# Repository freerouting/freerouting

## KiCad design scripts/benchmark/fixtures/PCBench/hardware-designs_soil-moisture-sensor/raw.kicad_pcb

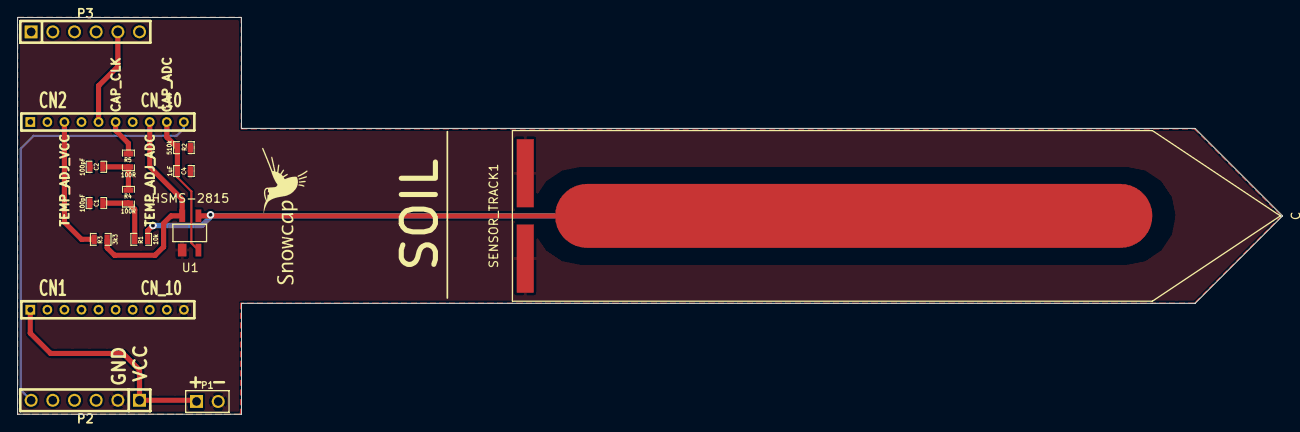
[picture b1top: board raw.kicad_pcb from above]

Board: 2 copper layers, 148.2 x 46.5 mm, 15 parts (0 on the bottom side), 11 nets.

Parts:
C1, C2: 100pF; SM0603_Capa
C4: 1uF; SM0603_Capa
CN1, CN2: CN_10; CONN-10-2MM
P1: CONN_2; PIN_ARRAY_2X1
P2, P3: CN_6; PIN_ARRAY-6X1
R1: 10k; SM0603_Resistor
R2: 510k; SM0603_Resistor
R3: 3k3; SM0603_Resistor
R4, R5: 100R; SM0603_Resistor
SENSOR_TRACK1: C; SOIL_SENSOR_CAPACITIVE
U1: HSMS-2815

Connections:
+3.3V: CN1.1, P1.1, P2.1
/CAP_ADC: C4.1, CN2.9, R2.1, U1.2
/CAP_CLK: CN2.6, R5.2
/TEMP_ADJ_ADC: CN2.8, R3.1, U1.3
/TEMP_ADJ_VCC: CN2.3, R3.2
/V_MEASURE1: CN2.10, P2.6
/V_MEASURE2: CN2.5, P3.5
GND: C1.1, C2.1, C4.2, CN1.10, P1.2, P2.2, R2.2, SENSOR_TRACK1.2, U1.1
unnamed: C2.2, R4.2, R5.1
unnamed: C1.2, R1.2, R4.1
unnamed: R1.1, SENSOR_TRACK1.1, U1.4

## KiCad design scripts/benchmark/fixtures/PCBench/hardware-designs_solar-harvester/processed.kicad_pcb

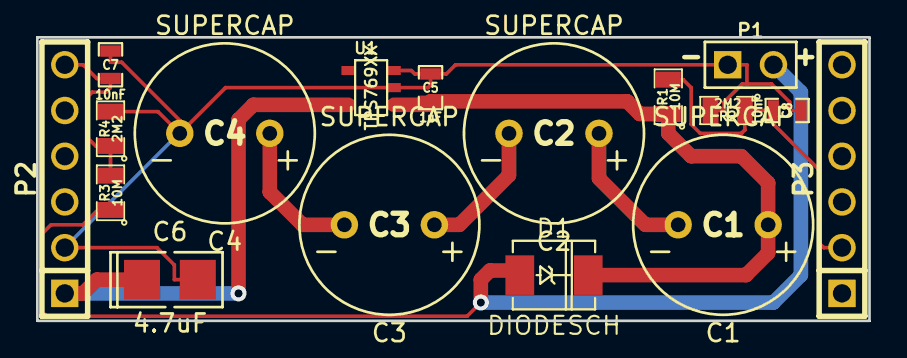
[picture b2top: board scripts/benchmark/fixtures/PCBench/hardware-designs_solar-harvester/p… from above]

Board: 2 copper layers, 46.2 x 15.7 mm, 18 parts (1 on the bottom side), 9 nets.

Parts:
C1, C2, C3, C4: SUPERCAP; SUPERCAP_ESHSR-0010C0-002R7
C5: 1uF; SM0603_Capa
C6: 4.7uF; SM1411_POL
C7, C8: 10nF; SM0603_Capa
D1: DIODESCH; DO-214AC(SMA)
Noname_1: LOGO_SNOWCAP_BACK
P1: CONN_2; PIN_ARRAY_2X1
P2, P3: CONN_6; PIN_ARRAY-6X1
R1, R3: 10M; SM0805
R2, R4: 2M2; SM0805
U1: TPS769XX; SOT23-5

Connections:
/V_MEASURE1: C7.1, P2.6, R3.2, R4.1
/V_MEASURE2: C8.1, P3.2, R1.2, R2.1
GND: C4.2, C5.2, C6.2, C7.2, C8.2, P1.1, P2.2, R2.2, R4.2, U1.2, U1.3
unnamed: C2.2, C3.1
unnamed: D1.1, P1.2, R3.1
unnamed: C6.1, P2.1, U1.5
unnamed: C1.2, C2.1
unnamed: C1.1, C5.1, D1.2, R1.1, U1.1
unnamed: C3.2, C4.1

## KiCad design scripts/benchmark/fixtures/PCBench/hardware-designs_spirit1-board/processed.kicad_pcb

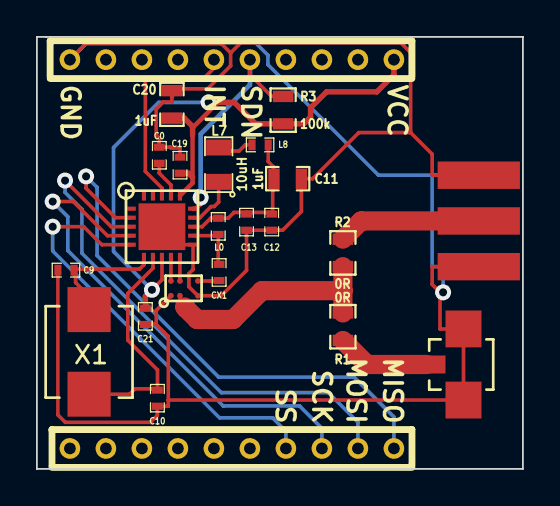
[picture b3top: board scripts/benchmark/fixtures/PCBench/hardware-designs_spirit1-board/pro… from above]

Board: 2 copper layers, 27.0 x 24.0 mm, 23 parts (1 on the bottom side), 21 nets.

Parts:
C0, C12: 100nF; SM0402_c
C9: 12pF; SM0402_c
C10: 10pF; SM0402_c
C11, C20: 1uF; SM0603_Capa
C13: 330pF; SM0402_c
C19: 10nF; SM0402_c
C21: 100pF; SM0402_c
CN1: RB-CN10; RB_CN10_2mm
CN2: ANT; RF_SMA
CN3: ANT; U.FL-R-SMT_01
CX1: C; SM0402_c
L0: 150nH; SM0402
L7: 10uH; SM0805
L8: 62nH; SM0402
Noname_1: LOGO_SNOWCAP_BACK
R1, R2: 0R; SM0603_Resistor
R3: 100k; SM0603_Resistor
U1: SPIRIT1; SPIRIT1_QFN20
U2: BALF-SPI-02D3; BALF_SPI_02D3
X1: 50Mhz; CRYSTAL-ABM3-50.000MHZ-D2Y-F-T

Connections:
/50ohm: R1.2, R2.1, U2.B1
GND: C0.2, C9.2, C10.2, C11.2, C12.2, C13.2, C19.2, C20.2, C21.2, CN1.10, CN2.2, CN3.2, U1.11, U1.21, U2.A1, U2.C1
unnamed: CN1.11, U1.2
unnamed: CN1.12, U1.3
unnamed: CN1.13, U1.4
unnamed: CN1.14, U1.5
unnamed: C0.1, U1.17
unnamed: CN1.5, R3.2, U1.15
unnamed: CN1.6, U1.18
unnamed: CN3.1, R1.1
unnamed: CN2.1, R2.2
unnamed: C11.1, C12.1, C13.1, L0.2, L8.2, U1.13
unnamed: L7.2, L8.1
unnamed: C9.1, U1.6, X1.1
unnamed: C10.1, U1.7, X1.2
unnamed: L7.1, U1.14
unnamed: U1.9, U2.A2
unnamed: U1.10, U2.B2
unnamed: CX1.1, L0.1, U1.12
unnamed: CX1.2, U2.C2
VCC: C19.1, C20.1, C21.1, CN1.1, R3.1, U1.8, U1.16
